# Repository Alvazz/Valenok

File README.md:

# Valenok
Zubax Valenok is a middle-power ESC for BLDC motors

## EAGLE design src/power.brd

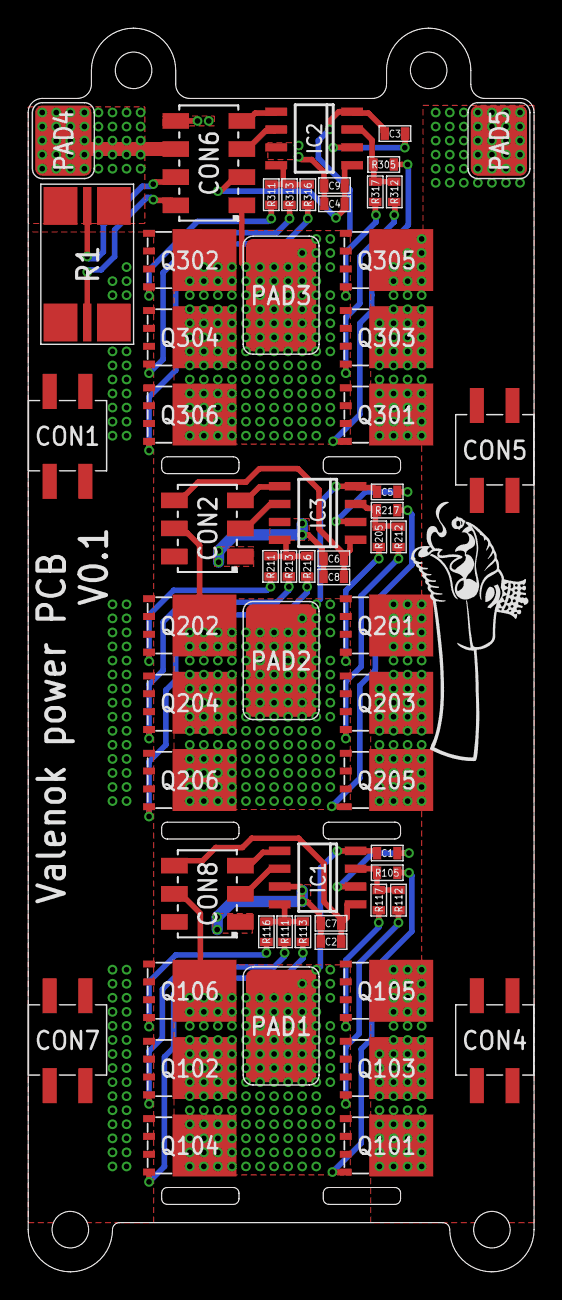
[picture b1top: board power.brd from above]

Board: 2 copper layers, 36.0 x 88.5 mm, 62 parts (0 on the bottom side), 45 nets.

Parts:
C1, C2, C3, C4, C5, C6: 0.1uF; C0603
C7, C8, C9: 1000pF; C0603
CON1, CON4, CON5, CON7: PINHEAD_2X02-SMD-2.54-MALE; PINHEAD_2X02_SMD_MALE_2.54
CON2, CON8: PINHEAD_2X03-0877590614; 2X03-SMD-2-MALE
CON6: PINHEAD_2X04-SMD-2-MALE; 2X04-SMD-2-MALE
IC1, IC2, IC3: UCC27282-SOIC8; SOIC8
PAD1, PAD2, PAD3: PAD-5X8; 5X8
PAD4, PAD5: PAD-5X4; 5X4
Q101, Q102, Q103, Q104, Q105, Q106, Q201, Q202, Q203, Q204, Q205, Q206, Q301, Q302, Q303, Q304, Q305, Q306: BSC077N12NS3GATMA1; PG-TDSON-8-1
R1: 200 µOhms; R3920-KELVIN
R105, R111, R112, R113, R116, R117, R205, R211, R212, R213, R216, R217, R305, R311, R312, R313, R316, R317: 4R3; R0603
U$1: DRAGON-18X7

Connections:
97: C2.1, C7.1, CON8.6, IC1.1
A_GH: IC1.3, R105.1, R112.1, R117.1
A_GL: IC1.8, R111.1, R113.1, R116.1
A_IH: CON8.5, IC1.5
A_IL: CON8.3, IC1.6
A_PH: C1.2, CON8.4, IC1.4, PAD1.P$1, Q101.1, Q101.2, Q101.3, Q102.P$1, Q103.1, Q103.2, Q103.3, Q104.P$1, Q105.1, Q105.2, Q105.3, Q106.P$1
B_GH: IC3.3, R205.1, R212.1, R217.1
B_GL: IC3.8, R211.1, R213.1, R216.1
B_IH: CON2.5, IC3.5
B_IL: CON2.3, IC3.6
B_PH: C5.2, CON2.4, IC3.4, PAD2.P$1, Q201.1, Q201.2, Q201.3, Q202.P$1, Q203.1, Q203.2, Q203.3, Q204.P$1, Q205.1, Q205.2, Q205.3, Q206.P$1
CS+: CON6.2, R1.S2
CS-: CON6.4, R1.S1
C_GH: IC2.3, R305.1, R312.1, R317.1
C_GL: IC2.8, R311.1, R313.1, R316.1
C_IH: CON6.7, IC2.5
C_IL: CON6.5, IC2.6
C_PH: C3.2, CON6.1, IC2.4, PAD3.P$1, Q301.1, Q301.2, Q301.3, Q302.P$1, Q303.1, Q303.2, Q303.3, Q304.P$1, Q305.1, Q305.2, Q305.3, Q306.P$1
GND: C2.2, C6.2, C7.2, C8.2, CON2.1, CON8.1, IC1.7, IC3.7
unnamed: C3.1, IC2.2
unnamed: C5.1, IC3.2
unnamed: C4.1, C9.1, CON6.3, IC2.1
unnamed: C6.1, C8.1, CON2.6, IC3.1
unnamed: C1.1, IC1.2
PGND: CON1.1, CON1.2, CON1.3, CON1.4, CON7.1, CON7.2, CON7.3, CON7.4, Q102.1, Q102.2, Q102.3, Q104.1, Q104.2, Q104.3, Q106.1, Q106.2, Q106.3, Q202.1, Q202.2, Q202.3, Q204.1, Q204.2, Q204.3, Q206.1, Q206.2, Q206.3, Q302.1, Q302.2, Q302.3, Q304.1, Q304.2, Q304.3, Q306.1, Q306.2, Q306.3, R1.2, R1.22
PHASE_A:N$1: Q101.4, R105.2
PHASE_A:N$2: Q102.4, R111.2
PHASE_A:N$3: Q103.4, R112.2
PHASE_A:N$4: Q104.4, R113.2
PHASE_A:N$5: Q105.4, R117.2
PHASE_A:N$6: Q106.4, R116.2
PHASE_B:N$1: Q201.4, R205.2
PHASE_B:N$2: Q202.4, R211.2
PHASE_B:N$3: Q203.4, R212.2
PHASE_B:N$4: Q204.4, R213.2
PHASE_B:N$5: Q205.4, R217.2
PHASE_B:N$6: Q206.4, R216.2
PHASE_C:N$1: Q301.4, R305.2
PHASE_C:N$2: Q302.4, R311.2
PHASE_C:N$3: Q303.4, R312.2
PHASE_C:N$4: Q304.4, R313.2
PHASE_C:N$5: Q305.4, R317.2
PHASE_C:N$6: Q306.4, R316.2
VBAT-: C4.2, C9.2, CON6.6, IC2.7, PAD4.P$1, R1.1, R1.11
VDC: CON4.1, CON4.2, CON4.3, CON4.4, CON5.1, CON5.2, CON5.3, CON5.4, CON6.8, PAD5.P$1, Q101.P$1, Q103.P$1, Q105.P$1, Q201.P$1, Q203.P$1, Q205.P$1, Q301.P$1, Q303.P$1, Q305.P$1

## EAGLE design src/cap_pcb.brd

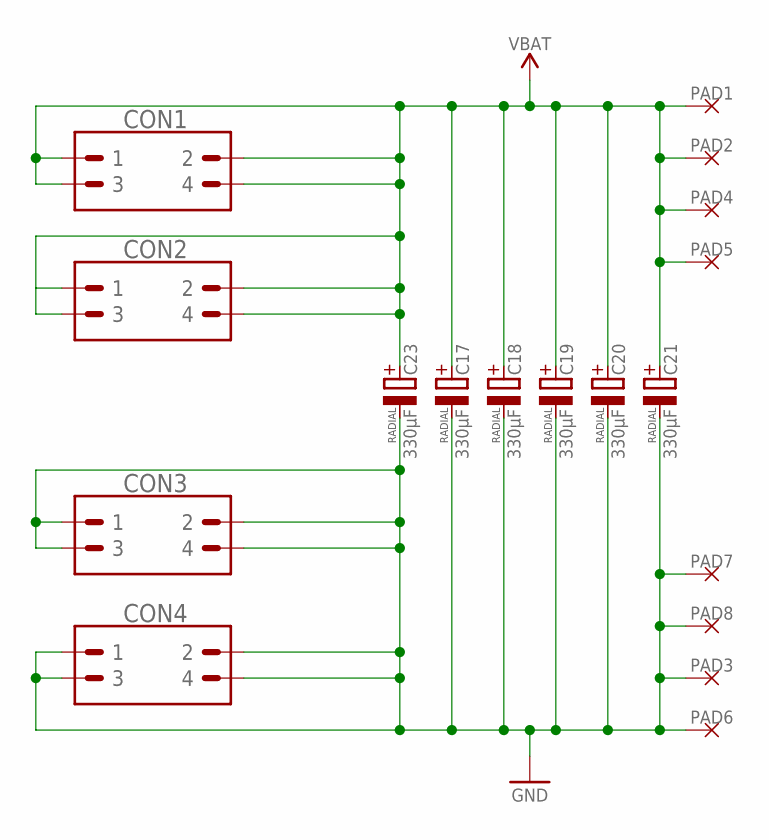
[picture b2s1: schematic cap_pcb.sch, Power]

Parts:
C17, C18, C19, C20, C21, C23: 330µF; RADIAL_SIDE_12.5X22; VOLTAGE 160V; DIGIKEY# 493-4784-3-ND
CON1, CON2, CON3, CON4: PINHEAD_2X02-PTH-2.54-MALE; 2X02-PTH-2.54
PAD1, PAD2, PAD3, PAD4, PAD5, PAD6, PAD7, PAD8: PAD-5X4; 5X4

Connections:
GND: C17.-, C18.-, C19.-, C20.-, C21.-, C23.-, CON3.1, CON3.2, CON3.3, CON3.4, CON4.1, CON4.2, CON4.3, CON4.4, PAD3.P$1, PAD6.P$1, PAD7.P$1, PAD8.P$1
VBAT: C17.+, C18.+, C19.+, C20.+, C21.+, C23.+, CON1.1, CON1.2, CON1.3, CON1.4, CON2.1, CON2.2, CON2.3, CON2.4, PAD1.P$1, PAD2.P$1, PAD4.P$1, PAD5.P$1

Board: 2 copper layers, 20 parts (11 on the bottom side), 2 nets, no tracks yet.

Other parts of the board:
U$1, U$3: ZUBAX_20X9

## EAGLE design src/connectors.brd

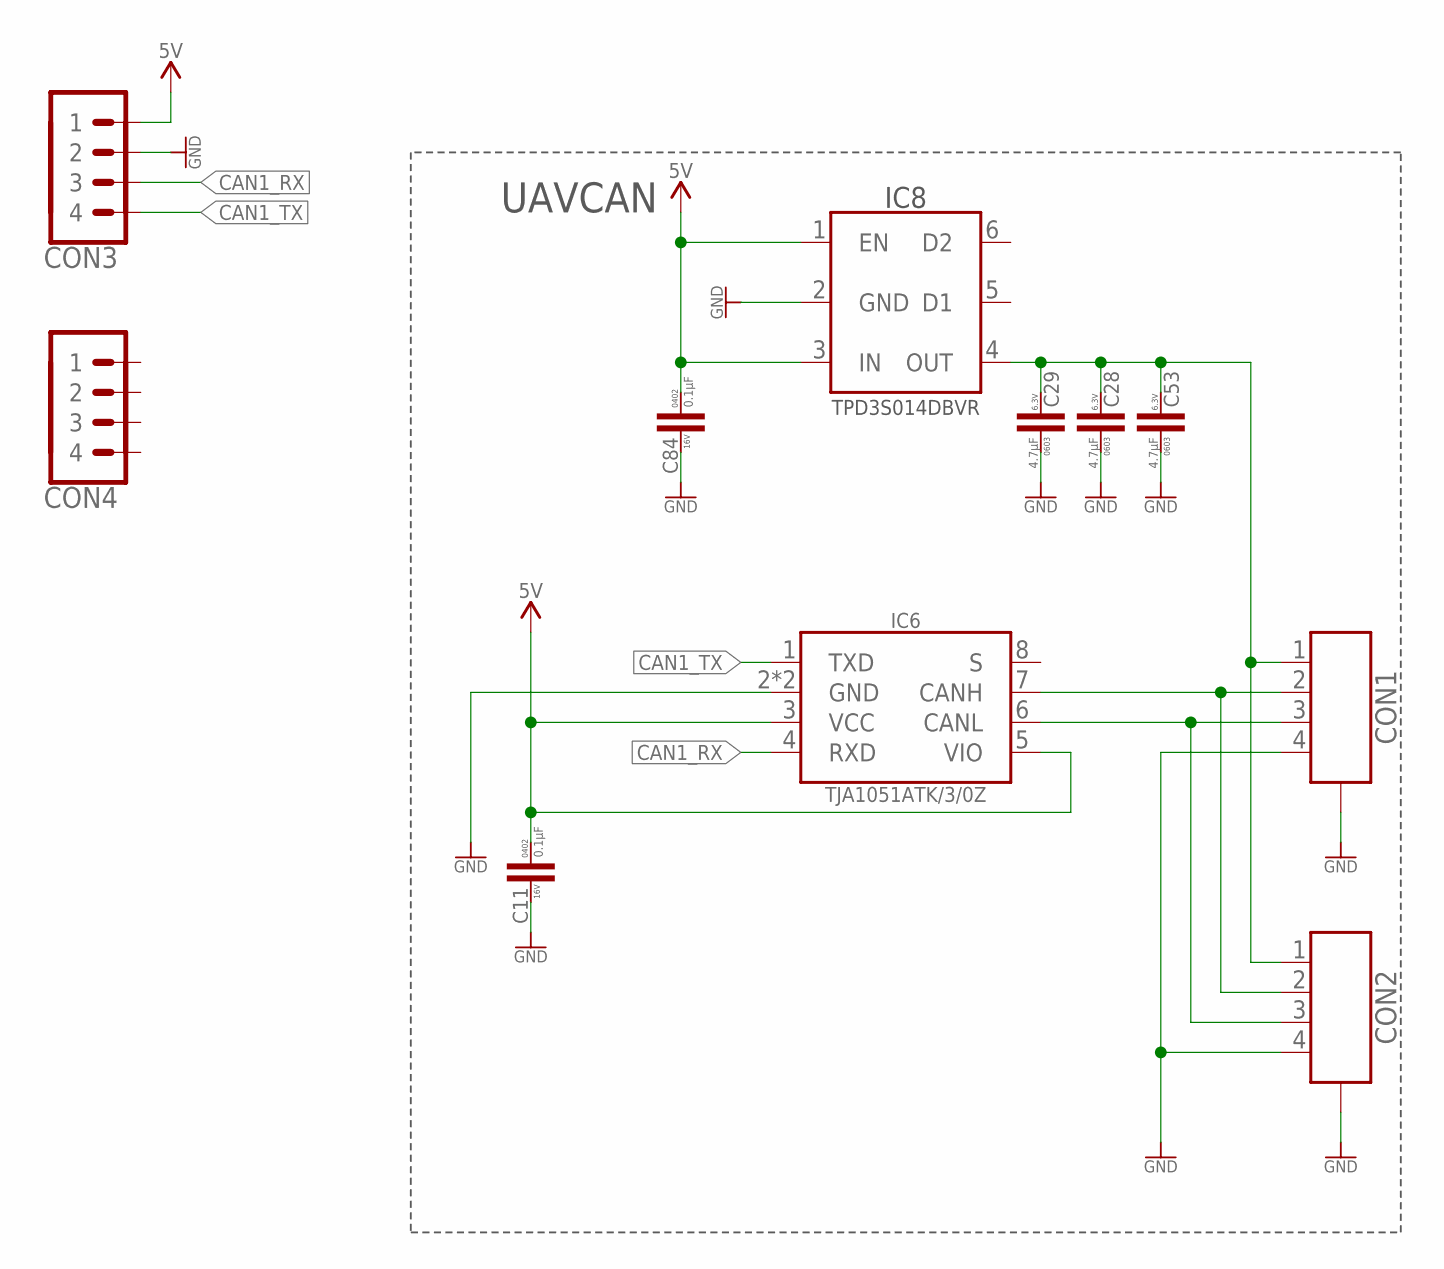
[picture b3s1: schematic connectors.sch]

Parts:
C11, C84: 0.1µF; C0402; VOLTAGE 16V; DIGIKEY# 490-3261-1-ND
C28, C29, C53: 4.7µF; C0603; VOLTAGE 6.3V; DIGIKEY# 1276-2087-1-ND
CON1, CON2: CON-4P-TABS-JST_GH-RA; JST_GH-4P-RA
CON3, CON4: PINHEAD_1X04-2-FEMALE; 1X04-PTH-2-FEMALE
IC6: TJA1051-HVSON8; SOT782-1
IC8: TPD3S014DBVR-SOT23-6; SOT26

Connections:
CAN1_RX: CON3.3, IC6.4 (RXD)
CAN1_TX: CON3.4, IC6.1 (TXD)
CAN1_VDD: C28.2, C29.2, C53.2, CON1.1, CON2.1, IC8.4 (OUT)
GND: C11.2, C28.1, C29.1, C53.1, C84.2, CON1.4, CON1.M$0 (GND), CON1.M$1 (GND), CON2.4, CON2.M$0 (GND), CON2.M$1 (GND), CON3.2, IC6.2 (GND), IC6.PAD (GND), IC8.2 (GND)
unnamed: CON1.2, CON2.2, IC6.7 (CANH)
unnamed: CON1.3, CON2.3, IC6.6 (CANL)
VDD_5V: C11.1, C84.1, CON3.1, IC6.3 (VCC), IC6.5 (VIO), IC8.1 (EN), IC8.3 (IN)

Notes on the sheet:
UAVCAN

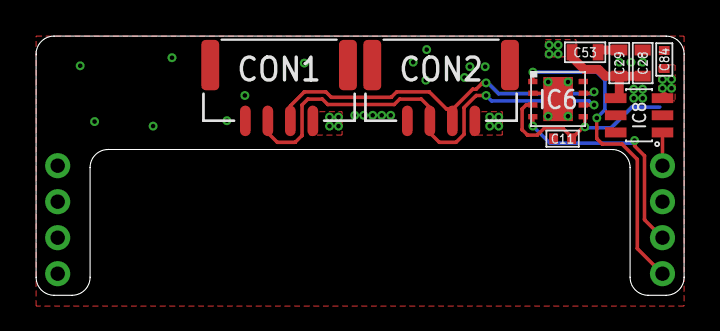
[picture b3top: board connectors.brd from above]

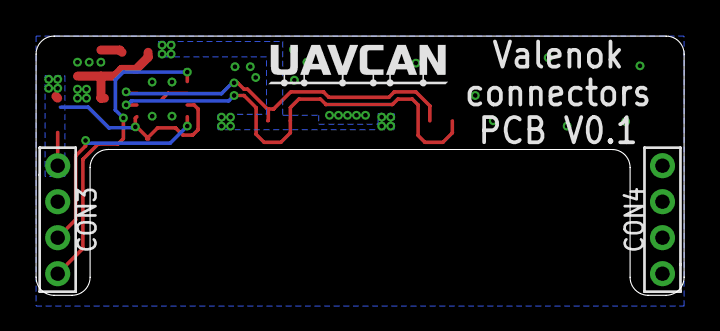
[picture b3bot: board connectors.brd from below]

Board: 2 copper layers, 36.0 x 14.4 mm, 12 parts (3 on the bottom side), 7 nets.

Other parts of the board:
U$1: UAVCAN_10X3

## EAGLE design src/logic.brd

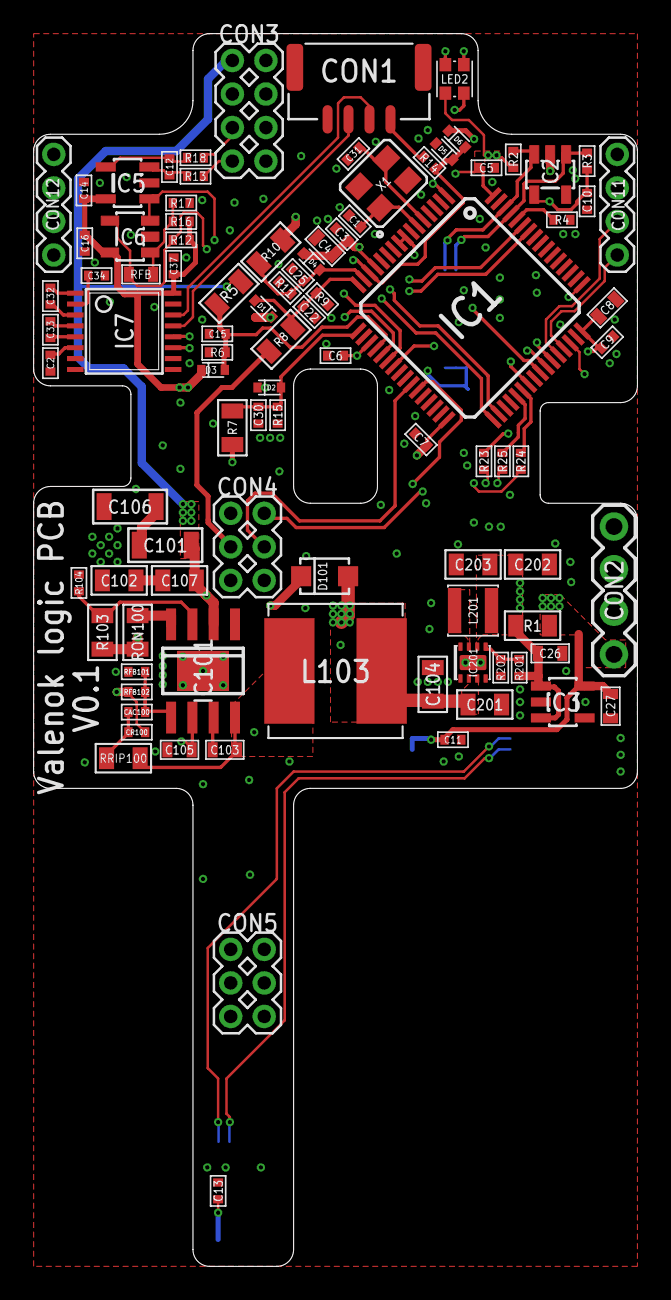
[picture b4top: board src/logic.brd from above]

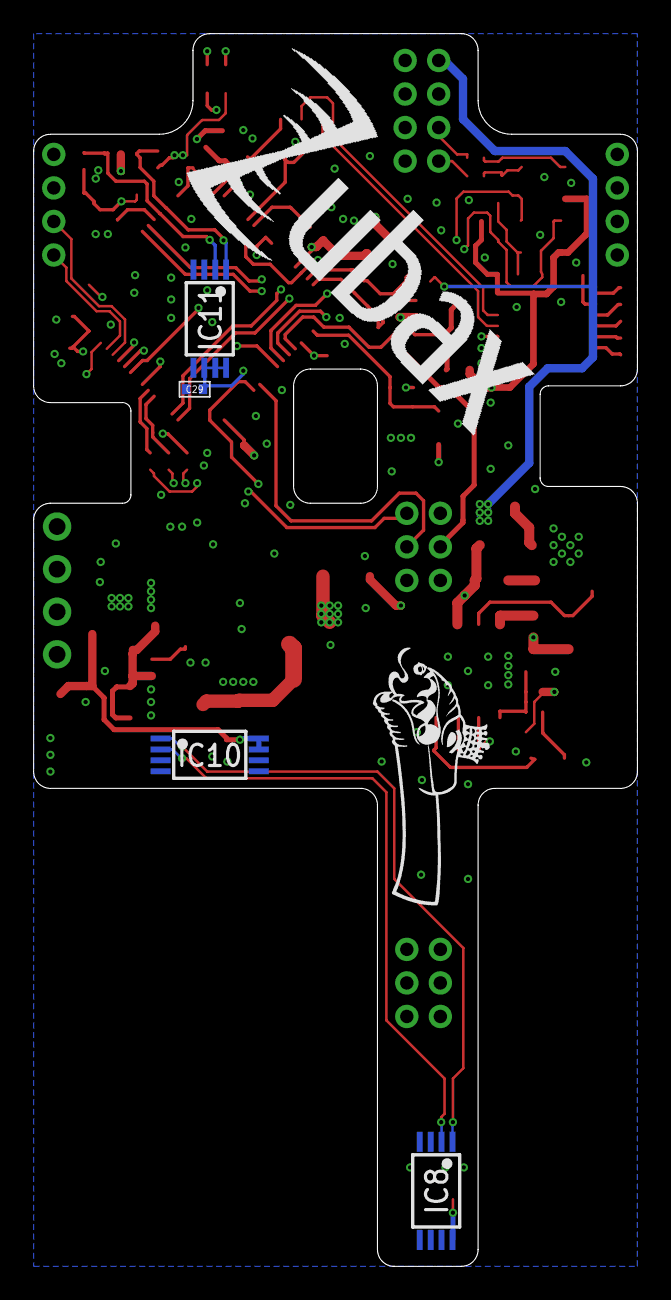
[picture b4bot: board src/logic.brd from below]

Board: 4 copper layers, 36.0 x 73.5 mm, 100 parts (6 on the bottom side), 65 nets.

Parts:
C1, C31: 9pF; C0402
C2, C5, C6, C7, C9, C10, C11, C13, C14, C16, C29, C32, C33, C34, C37: 0.1µF; C0402
C3: 10nF; C0402
C4, C26, C105: 1µF; C0603
C8, C27: 4.7µF; C0603
C12: 1000pF; C0402
C15, C22, C25, C30: 4700pF; C0402
C101, C106: 4.7µF; C1206
C102, C107: 1µF; C0805
C103: 0.01uF; C0603
C104, C201, C202, C203: 10uF; C0805
CAC100: 0.1uF; C0402
CON1: CON-4P-TABS-JST_GH-RA; JST_GH-4P-RA
CON2: PINHEAD_1X04-2.54; 1X04-PTH-2.54
CON3: PINHEAD_2X04-PLS-2; 2X04-PTH-2
CON4, CON5: PINHEAD_2X03-PTH-2; 2X03-PTH-2
CON11, CON12: PINHEAD_1X04-2; 1X04-PTH-2
CR100: 3300pF; C0402
D1, D2, D3, D4, D5, D6: BAT54KFILM; SOD523
D101: PMEG4020; SOD123F
IC1: STM32F105RCT6; TQFP64
IC2: CAT24C02; SOT23-5L
IC3: AP2127-3.3; SOT23-5
IC5: INA180A2; SOT23-5
IC6: LMV331; SOT23-5L
IC7: ST3232; TSSOP16
IC8, IC10, IC11: LM75-TSSOP8; TSSOP8
IC101: LM5017; SOIC8-POWERPAD
IC201: TPS62160QDSGRQ1; WFDFN-8
L103: 120µH; HPC8040NF
L201: 2.2µH; NR3015
LED2: LED_RGB-2020; LED2020
R1: DNM; R0805
R2, R3, R4: 3K9; R0402
R5: 110K; R0805
R6, R16: 3K3; R0402
R7, R8, R10: 51K; R0805
R9, R11, R15: 1K8; R0402
R12, R17: 5K6; R0402
R13, R18: 000; R0402
R14, R23, R24, R25: 200R; R0402
R103: 127K; R0805
R104: 14K; R0402
R201: 51K; R0402
R202: 10K; R0402
RFB: DNM; R0603
RFB101: 1K; R0402
RFB102: 10K; R0402
RON100: 110K; R0805
RRIP100: 110K; R0805
U$1: DRAGON-15X6
U$2: ZUBAX_25X12
X1: 16MHz; OSCILLATOR-3.2X2.5-4P

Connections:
BOOT0: IC1.60, R4.2
CAN1_RX: CON11.3, IC1.44
CAN1_TX: CON11.4, IC1.45
CAN2_RX: CON12.3, IC1.33
CAN2_TX: CON12.4, IC1.34
CS+: C12.1, IC5.3, R13.1
CS-: C12.2, IC5.4, R18.1
CURRENT_AMP_OUT: IC1.21, IC5.1, IC6.3
FET_A_H: CON3.2, IC1.41
FET_A_L: CON3.4, IC1.23
FET_B_H: CON4.2, IC1.42
FET_B_L: CON4.4, IC1.26
FET_C_H: CON5.2, IC1.43
FET_C_L: CON5.4, IC1.27
GND: C1.1, C2.2, C3.1, C4.1, C5.1, C6.1, C7.1, C8.2, C9.2, C10.2, C11.2, C13.2, C14.2, C15.1, C16.1, C22.1, C25.1, C26.1, C27.1, C29.2, C30.1, C31.1, C34.2, C37.1, C102.1, C104.1, C105.1, C106.P$1, C201.1, C202.1, C203.1, CON1.4, CON1.M$0, CON1.M$1, CON2.3, CON3.3, CON4.5, CON4.6, CON5.5, CON5.6, CON11.2, CON12.2, D5.A, IC1.10, IC1.11, IC1.12, IC1.18, IC1.31, IC1.47, IC1.63, IC2.2, IC3.2, IC5.2, IC6.2, IC7.15, IC8.4, IC8.5, IC8.6, IC8.7, IC10.4, IC10.5, IC10.6, IC11.4, IC11.5, IC101.1, IC101.P$1, IC201.1, IC201.4, IC201.EP, R4.1, R6.1, R9.1, R11.1, R15.1, R17.2, R104.1, R202.1, RFB101.1, X1.2, X1.4
HV_DC-DC(LM5017):N$1: C101.P$1, C106.P$2
HV_DC-DC(LM5017):N$2: C103.2, IC101.8, L103.1, RRIP100.2
HV_DC-DC(LM5017):N$3: CAC100.2, CR100.2, RRIP100.1
HV_DC-DC(LM5017):N$4: C102.2, C107.1
HV_DC-DC(LM5017):N$10: C105.2, D101.C, IC101.6
HV_DC-DC(LM5017):N$11: IC101.4, RON100.2
HV_DC-DC(LM5017):N$12: C103.1, IC101.7
HV_DC-DC(LM5017):N$14: CAC100.1, IC101.5, RFB101.2, RFB102.1
HV_DC-DC(LM5017):N$17: IC101.3, R103.1, R104.2
I2C_SCL: IC1.61, IC2.1, IC8.2, IC10.2, IC11.2, R3.2
I2C_SDA: IC1.62, IC2.3, IC8.1, IC10.1, IC11.1, R2.2
LV_DC-DC:FB: IC201.5, R201.1, R202.2
LV_DC-DC:N$1: IC201.7, L201.1
unnamed: CON3.7, R13.2
unnamed: CON1.1, R14.1
unnamed: IC1.37, R25.2
unnamed: CON3.5, R18.2
unnamed: LED2.B, R23.1
unnamed: LED2.R, R25.1
unnamed: IC1.38, R24.2
unnamed: C31.2, IC1.5, X1.3
unnamed: IC1.39, R23.2
unnamed: C32.1, IC7.1
unnamed: C32.2, IC7.3
unnamed: C1.2, IC1.6, X1.1
unnamed: C33.1, IC7.5
unnamed: C33.2, IC7.4
unnamed: LED2.G, R24.1
unnamed: C2.1, IC7.6
unnamed: C34.1, IC7.2
unnamed: CON1.3, IC7.13
unnamed: CON1.2, IC7.14
OVERCURRENT_FAULT: IC1.22, IC6.4, R12.2, RFB.1
PHASE_A: CON3.8, R10.1
PHASE_B: CON4.3, R8.1
PHASE_C: CON5.3, R7.1
RC_PWM: CON12.1, D5.C, D6.A, IC1.14, R14.2
SENSE_A: C25.2, D4.A, IC1.15, R10.2, R11.2
SENSE_B: C22.2, D1.A, IC1.16, R8.2, R9.2
SENSE_C: C30.2, D2.A, IC1.17, R7.2, R15.2
SENSE_VIN: C15.2, D3.A, IC1.20, R5.1, R6.2
SWCLK: CON2.2, IC1.49
SWDIO: CON2.1, IC1.46
USART1_RX: IC1.59, IC7.12
USART1_TX: IC1.58, IC7.11
VDC: C101.P$2, C107.2, CON3.1, IC101.2, R5.2, R103.2, RON100.1
VDD_3V3: C3.2, C4.2, C5.2, C6.2, C7.2, C8.1, C9.1, C10.1, C11.1, C13.1, C14.1, C16.2, C27.2, C29.1, C37.2, CON2.4, D1.C, D2.C, D3.C, D4.C, IC1.1, IC1.8, IC1.9, IC1.13, IC1.19, IC1.32, IC1.48, IC1.64, IC2.4, IC3.5, IC5.5, IC6.5, IC7.16, IC8.8, IC10.7, IC10.8, IC11.6, IC11.7, IC11.8, LED2.+, R1.2, R2.1, R3.1, R12.1, R16.2
VDD_5V: C26.2, C202.2, C203.2, CON11.1, D6.C, IC3.1, IC3.3, IC201.6, L201.2, R1.1, R201.2
VDD_12V: C104.2, C201.2, CON3.6, CON4.1, CON5.1, CR100.1, D101.A, IC201.2, IC201.3, L103.2, RFB102.2
VREF: IC6.1, R16.1, R17.1, RFB.2

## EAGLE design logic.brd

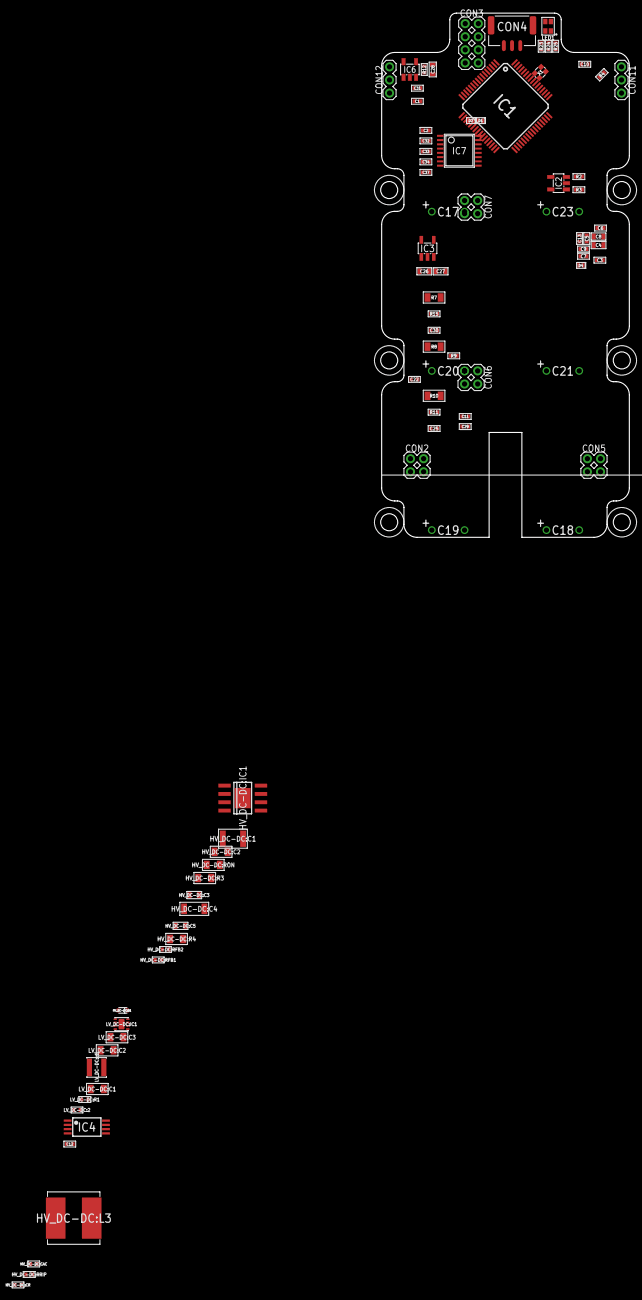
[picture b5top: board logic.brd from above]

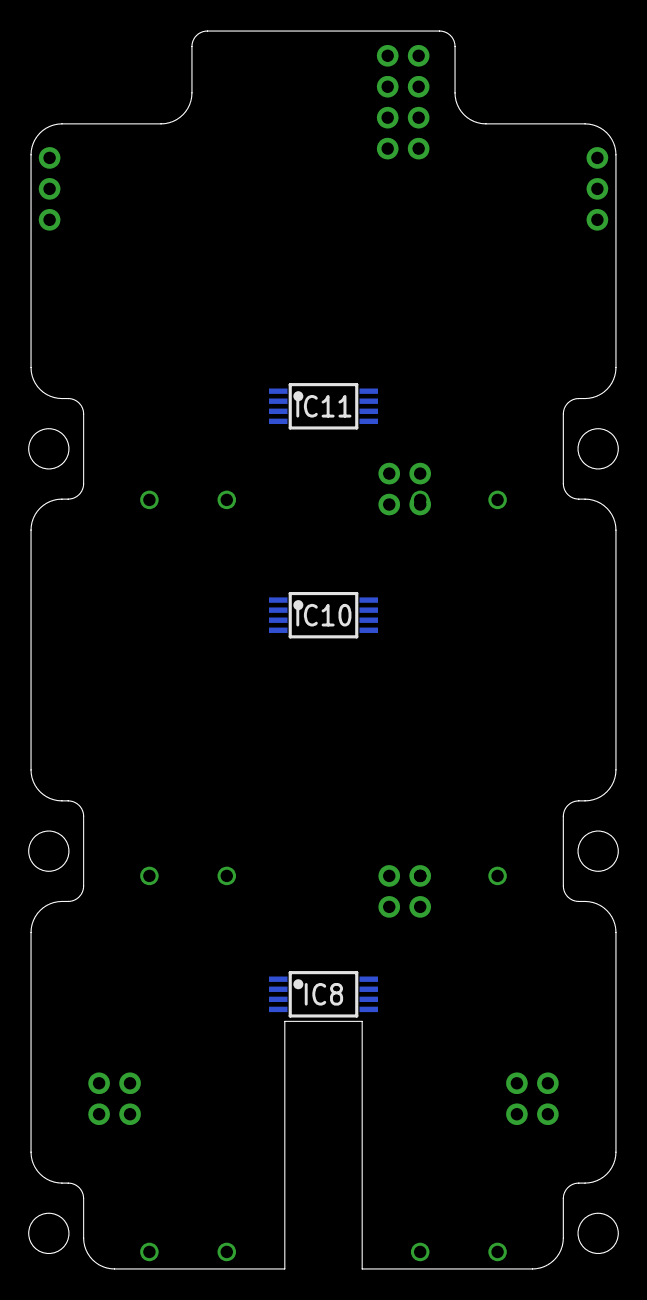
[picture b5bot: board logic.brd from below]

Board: 4 copper layers, 37.8 x 80.0 mm, 89 parts (3 on the bottom side), 40 nets, no tracks yet.

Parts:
C1, C31: 18pF; C0402
C2, C5, C6, C7, C9, C10, C11, C12, C13, C29, C32, C33, C34, C37: 0.1µF; C0402
C3: 10nF; C0402
C4, C26, C28: 1µF; C0603
C8, C27: 4.7µF; C0603
C17, C18, C19, C20, C21, C23: 100µF; RADIAL_SIDE_12.5X22
C22, C25, C30: 1800pF; C0402
CON2, CON5, CON6, CON7: PINHEAD_2X02-PTH-2-MALE; 2X02-PTH-2
CON3: PINHEAD_2X04-PLS-2; 2X04-PTH-2
CON4: CON-3P-TABS; JST_GH-3P-RA
CON11, CON12: PINHEAD_1X03-2; 1X03-PTH-2
D1, D2, D4: BAS16L; SOD882
HV_DC-DC:C1: 2.2uF; C1210
HV_DC-DC:C2: 0.47uF; C0805
HV_DC-DC:C3: 0.01uF; C0603
HV_DC-DC:C4: 10uF; C1206
HV_DC-DC:C5: 1uf; C0603
HV_DC-DC:CAC: 0.1uF; C0402
HV_DC-DC:CR: 3300pF; C0402
HV_DC-DC:D1: PMEG3005; SOD523
HV_DC-DC:IC1: LM5017; SOIC8-POWERPAD
HV_DC-DC:L3: 120µH; HPC8040NF
HV_DC-DC:R3: 127K; R0805
HV_DC-DC:R4: 14K; R0805
HV_DC-DC:RFB1: 1K; R0402
HV_DC-DC:RFB2: 3K; R0402
HV_DC-DC:RON: 110K; R0805
HV_DC-DC:RRIP: 110K; R0402
IC1: STM32F105RCT6; TQFP64
IC2: CAT24C02; SOT23-5L
IC3: AP2127-3.3; SOT23-5
IC4, IC8, IC10, IC11: LM75-TSSOP8; TSSOP8
IC6: ZXCT1051; SOT23-5L
IC7: ST3232; TSSOP16
LED1: LTST-C19HE1WT; 0606
LV_DC-DC:2: 10K; R0402
LV_DC-DC:C1, LV_DC-DC:C2, LV_DC-DC:C3: 10uF; C0805
LV_DC-DC:IC1: TPS62160QDSGRQ1; WFDFN-8
LV_DC-DC:L1: 2.2µH; NR3015
LV_DC-DC:R1: 51K; R0402
R2, R3, R4, R12: 3K9; R0402
R7, R8, R10: 4K7; R0805
R9, R11, R15: 560R; R0402
R23, R24, R25: 200R; R0402
X1: 16MHz; OSCILLATOR-2.0X1.6-4P

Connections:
BLABLA: IC6.3, R12.1
BOOT0: IC1.60, R4.2
GND: C1.1, C2.2, C3.1, C4.1, C5.1, C6.1, C7.1, C8.2, C9.2, C10.2, C11.2, C12.2, C13.2, C17.-, C18.-, C19.-, C20.-, C21.-, C22.1, C23.-, C25.1, C26.1, C27.1, C28.P$1, C29.2, C30.1, C31.1, C34.2, C37.1, CON4.3, CON4.M$0, CON4.M$1, HV_DC-DC:C1.1, HV_DC-DC:C2.1, HV_DC-DC:C4.P$1, HV_DC-DC:C5.1, HV_DC-DC:IC1.1, HV_DC-DC:IC1.P$1, HV_DC-DC:R4.1, HV_DC-DC:RFB1.1, IC1.10, IC1.11, IC1.12, IC1.18, IC1.31, IC1.47, IC1.63, IC2.2, IC3.2, IC4.4, IC6.2, IC7.15, IC8.4, IC8.5, IC8.6, IC8.7, IC10.4, IC10.5, IC10.6, IC11.4, IC11.5, LV_DC-DC:2.1, LV_DC-DC:2.2, LV_DC-DC:C1.1, LV_DC-DC:C2.1, LV_DC-DC:C3.1, LV_DC-DC:IC1.1, LV_DC-DC:IC1.4, LV_DC-DC:IC1.5, LV_DC-DC:IC1.EP, LV_DC-DC:R1.1, R4.1, R9.1, R11.1, R15.1, X1.2, X1.4
HV_DC-DC:N$2: HV_DC-DC:C3.2, HV_DC-DC:IC1.8, HV_DC-DC:L3.1, HV_DC-DC:RRIP.2
HV_DC-DC:N$3: HV_DC-DC:CAC.2, HV_DC-DC:CR.2, HV_DC-DC:RRIP.1
HV_DC-DC:N$10: HV_DC-DC:C5.2, HV_DC-DC:D1.C, HV_DC-DC:IC1.6
HV_DC-DC:N$11: HV_DC-DC:IC1.4, HV_DC-DC:RON.2
HV_DC-DC:N$12: HV_DC-DC:C3.1, HV_DC-DC:IC1.7
HV_DC-DC:N$14: HV_DC-DC:CAC.1, HV_DC-DC:IC1.5, HV_DC-DC:RFB1.2, HV_DC-DC:RFB2.1
HV_DC-DC:N$17: HV_DC-DC:IC1.3, HV_DC-DC:R3.1, HV_DC-DC:R4.2
I2C_SCL: IC1.61, IC2.1, IC4.2, IC8.2, IC10.2, IC11.2, R3.2
I2C_SDA: IC1.62, IC2.3, IC4.1, IC8.1, IC10.1, IC11.1, R2.2
LV_DC-DC:N$1: LV_DC-DC:IC1.7, LV_DC-DC:L1.1
unnamed: IC1.37, R25.2
unnamed: LED1.B, R23.1
unnamed: LED1.R, R25.1
unnamed: IC1.38, R24.2
unnamed: C31.2, IC1.5, X1.3
unnamed: IC1.39, R23.2
unnamed: C32.1, IC7.1
unnamed: C32.2, IC7.3
unnamed: C1.2, IC1.6, X1.1
unnamed: C33.1, IC7.5
unnamed: C33.2, IC7.4
unnamed: LED1.G, R24.1
unnamed: C2.1, IC7.6
unnamed: C34.1, IC7.2
unnamed: CON4.2, IC7.13
unnamed: CON4.1, IC7.14
SENSE_A: C30.2, D2.A, IC1.15, R7.2, R15.2
SENSE_B: C22.2, D1.A, IC1.16, R8.2, R9.2
SENSE_C: C25.2, D4.A, IC1.17, R10.2, R11.2
SENSE_CURRENT: C28.P$2, IC1.21, R12.2
USART1_RX/PWM: IC1.14, IC1.59, IC7.12
USART1_TX: IC1.58, IC7.11
VBAT: C17.+, C18.+, C19.+, C20.+, C21.+, C23.+
VDC: HV_DC-DC:C1.2, HV_DC-DC:C2.2, HV_DC-DC:IC1.2, HV_DC-DC:R3.2, HV_DC-DC:RON.1
VDD_3V3: C3.2, C4.2, C5.2, C6.2, C7.2, C8.1, C9.1, C10.1, C11.1, C12.1, C13.1, C27.2, C29.1, C37.2, D1.C, D2.C, D4.C, IC1.1, IC1.8, IC1.9, IC1.13, IC1.19, IC1.32, IC1.48, IC1.64, IC2.4, IC3.5, IC4.5, IC4.6, IC4.7, IC4.8, IC6.1, IC7.16, IC8.8, IC10.7, IC10.8, IC11.6, IC11.7, IC11.8, LED1.+, R2.1, R3.1
VDD_5V: C26.2, IC3.1, IC3.3, LV_DC-DC:C2.2, LV_DC-DC:C3.2, LV_DC-DC:IC1.6, LV_DC-DC:L1.2, LV_DC-DC:R1.2
VDD_12V: HV_DC-DC:C4.P$2, HV_DC-DC:CR.1, HV_DC-DC:D1.A, HV_DC-DC:L3.2, HV_DC-DC:RFB2.2, LV_DC-DC:C1.2, LV_DC-DC:IC1.2, LV_DC-DC:IC1.3

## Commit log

2020-09-25 Update LICENSE
2020-09-27 hardware requirements initial commit
2020-09-29 high-level requirements update
2020-10-09 initial import
2020-10-16 attribute updates
2020-10-17 Create implementation_requirements
2020-10-17 Rename implementation_requirements to implementation_requirements.md
2020-10-18 Figures added
2020-10-20 Update and rename high-level requirements.md to high-level_requirements.md
    Добавил требования надёжности, внёс несколько малозначимых изменений в раздел про интерфейсы, поправил форматирование и пунктуацию.
2020-10-22 Power supply scheme rearrangement
2020-10-23 HV dc-dc update
2020-10-23 Attributes extension
2020-10-26 Update high-level_requirements.md
    UART => RS-485/232
2020-10-26 cleanup
2020-10-28 Connectors update
2020-10-29 Components placement
2020-10-29 outline update
2020-11-02 Updates here and there
2020-11-04 routing upodates
2020-11-05 Currennt measurement update
2020-11-05 experimental digital pot added
2020-11-05 bigger connector PCB connectors
2020-11-09 logic pcb routing done
2020-11-10 connectors PCB routing effort
2020-11-10 connectors pcb adjustments
2020-11-13 rearrangement and alternate power stage design added
2020-11-13 Minor updates
2020-11-13 variant A updates
2020-11-13 Remove version A
2020-11-16 BEMF sensig nets updates
2020-11-16 capacitor PCB polygons update
2020-11-16 Current amplifier input filtering added
2020-11-16 Logic PCB updates
2020-11-16 Logos added
2020-11-16 Connectors PCB UAVCAN logo added
2020-11-16 Power PCB update
    DRC errors resolvinnng
2020-11-16 Silkscreen updates
2020-11-16 Values of the current amp filter updated
2020-11-17 phase sensing nominals updated
2020-11-17 Phase sensing filter update
2020-11-17 BEMF filter update
2020-11-17 cosmetics
2020-11-19 massibe attribute updates everywhere
2020-11-19 Minor attribute tweaks
2020-11-19 minor fix
2020-11-20 HV Capacitors optimizations
2020-11-20 Interpcb connectors updated. Ground problem solved
2020-11-20 Slots update
2020-11-20 attributes update
2020-11-23 RC PWM updated
2020-11-23 Tools added
2020-11-23 Crystal attributes update
2020-11-24 Massive routing update
    InterPCB connectors between Cap PCB and power PCB replaced with bigger ones
2020-11-25 DC-DC design notes update
2020-11-25 Notes added
2020-11-25 assembly variant fix
2020-11-25 Update logic.brd
    Minor outline correction
2020-11-25 assembly variant update
2020-11-25 Outline updates to allow debug assembly with connectors
2020-11-25 Connectors PCB pinheaders updated
2020-12-03 Minor tweaks here and there for better manufacturability
